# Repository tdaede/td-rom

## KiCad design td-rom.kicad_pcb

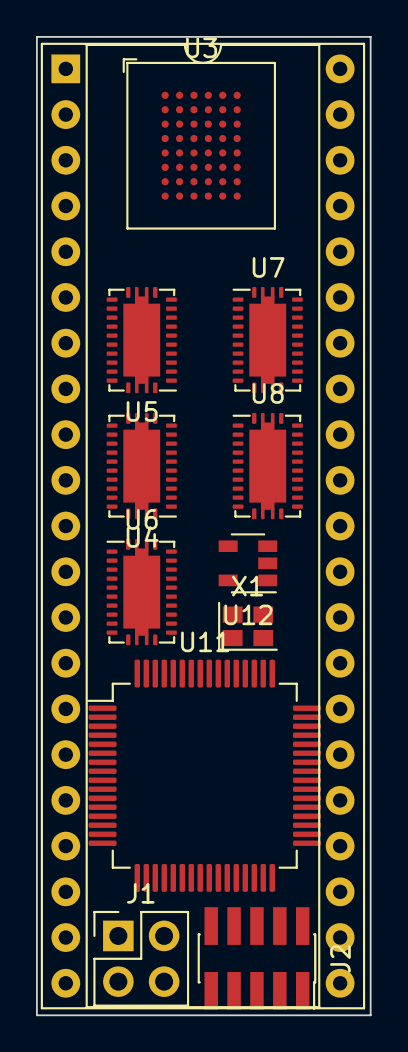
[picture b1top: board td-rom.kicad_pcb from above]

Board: 4 copper layers, 18.5 x 54.4 mm, 12 parts (0 on the bottom side), 47 nets, no tracks yet.

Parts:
J1: Conn_02x02_Odd_Even; PinHeader_2x02_P2.54mm_Vertical
J2: Conn_ARM_JTAG_SWD_10; PinSocket_2x05_P1.27mm_Vertical_SMD
U2: TC5364205; DIP-42_W15.24mm_Socket
U3: IS66WVE4M16TBLL-70BLI; BGA-48_8.0x9.0mm_Layout6x8_P0.8mm
U4, U5, U6, U7, U8: SN74AVC8T245PW; Texas_VQFN-RHL-24
U11: STM32L052R8Tx; LQFP-64_10x10mm_P0.5mm
U12: TPS76933; SOT-23-5
X1: SG-210SCD; Oscillator_SMD_SeikoEpson_SG210-4Pin_2.5x2.0mm

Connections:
+3V3: U3.D6, U3.E1
/5v_a0: U2.10, U4.15
/5v_a1: U2.9, U4.16
/5v_a2: U2.8, U4.17
/5v_a3: U2.7, U4.18
/5v_a4: U2.6, U4.19
/5v_a5: U2.5, U4.20
/5v_a6: U2.4, U4.21
/5v_a7: U2.3, U5.14
/5v_a8: U2.41, U5.18
/5v_a9: U2.40, U5.19
/5v_a10: U2.39, U7.14
/5v_a11: U2.38, U7.15
/5v_a12: U2.37, U7.16
/5v_a13: U2.36, U7.17
/5v_a14: U2.35, U7.18
/5v_a15: U2.34, U7.19
/5v_a16: U2.33, U7.20
/5v_a17: U2.2, U5.15
/5v_a18: U2.1, U5.16
/5v_a19: U2.42, U5.17
/5v_a20: U2.32, U7.21
/5v_a21: U2.13, U4.14
/5v_dq0: U2.14, U6.10
/5v_dq1: U2.16, U6.8
/5v_dq2: U2.18, U6.6
/5v_dq3: U2.20, U6.4
/5v_dq4: U2.23, U8.10
/5v_dq5: U2.25, U8.8
/5v_dq6: U2.27, U8.6
/5v_dq7: U2.29, U8.4
/5v_dq8: U2.15, U6.9
/5v_dq9: U2.17, U6.7
/5v_dq10: U2.19, U6.5
/5v_dq11: U2.21, U6.3
/5v_dq12: U2.24, U8.9
/5v_dq13: U2.26, U8.7
/5v_dq14: U2.28, U8.5
/5v_dq15: U2.30, U8.3
/~5v_e: U2.11, U5.20
GND: U2.12, U2.31, U3.D1, U3.E6
unnamed: J2.3, J2.5
unnamed: U4.11, U4.12, U4.13
unnamed: U5.11, U5.12, U5.13
unnamed: U6.11, U6.12, U6.13
unnamed: U7.11, U7.12, U7.13
unnamed: U8.11, U8.12, U8.13
